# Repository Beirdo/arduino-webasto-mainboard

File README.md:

# arduino-webasto-mainboard
Custom replacement control board for Webasto Thermo Top C/E

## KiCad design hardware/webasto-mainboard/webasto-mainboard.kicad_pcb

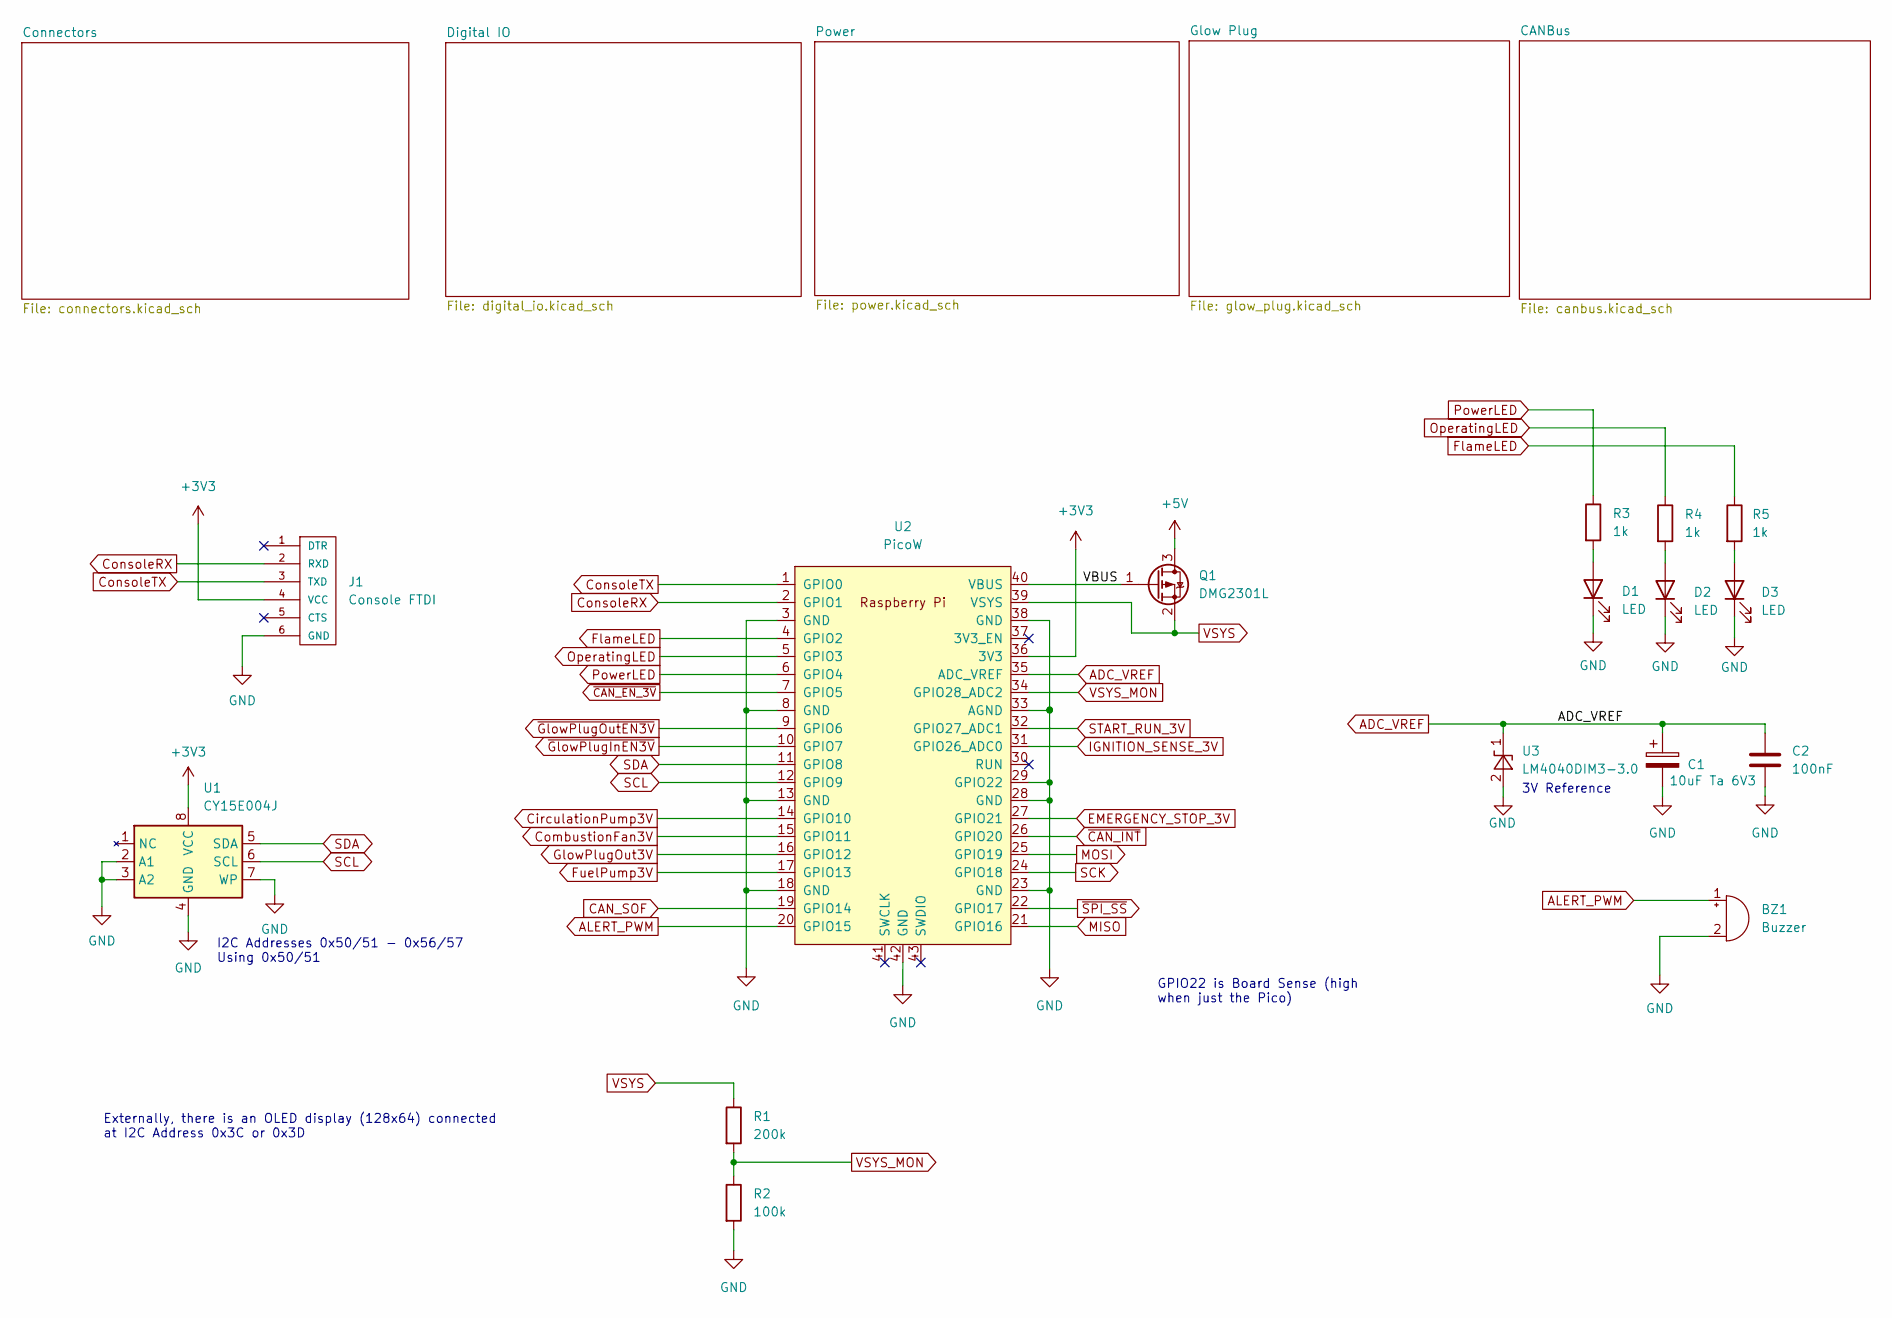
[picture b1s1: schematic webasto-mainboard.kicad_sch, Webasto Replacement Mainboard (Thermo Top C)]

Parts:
BZ1: Buzzer; Buzzer_TDK_PS1240P02BT_D12.2mm_H6.5mm
C1: 10uF Ta 6V3; CP_EIA-3216-10_Kemet-I_Pad1.58x1.35mm_HandSolder
C2: 100nF; C_0805_2012Metric_Pad1.18x1.45mm_HandSolder
D1, D2, D3: LED; LED_0805_2012Metric_Pad1.15x1.40mm_HandSolder
J1: Console FTDI; FTDI-TARGET
Q1: DMG2301L; SOT-23
R1: 200k; R_0805_2012Metric_Pad1.20x1.40mm_HandSolder
R2: 100k; R_0805_2012Metric_Pad1.20x1.40mm_HandSolder
R3, R4, R5: 1k; R_0805_2012Metric_Pad1.20x1.40mm_HandSolder
U1: CY15E004J; SOIC-8_5.23x5.23mm_P1.27mm
U2: PicoW; RPi_Pico_SMD_TH
U3: LM4040DIM3-3.0; SOT-23

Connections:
+3V3: J1.4 (VCC), U1.8 (VCC), U2.36 (3V3); also elsewhere on the board
+5V: Q1.3 (D); also elsewhere on the board
/VBUS: Q1.1 (G), U2.40 (VBUS)
ADC_VREF: C1.1, C2.1, U2.35 (ADC_VREF), U3.1 (K)
ALERT_PWM: BZ1.1 (-), U2.20 (GPIO15)
CAN_SOF: U2.19 (GPIO14); also elsewhere on the board
CirculationPump3V: U2.14 (GPIO10); also elsewhere on the board
CombustionFan3V: U2.15 (GPIO11); also elsewhere on the board
ConsoleRX: J1.2 (RXD), U2.2 (GPIO1)
ConsoleTX: J1.3 (TXD), U2.1 (GPIO0)
EMERGENCY_STOP_3V: U2.27 (GPIO21); also elsewhere on the board
FlameLED: R5.1, U2.4 (GPIO2)
FuelPump3V: U2.17 (GPIO13); also elsewhere on the board
GND: BZ1.2 (+), C1.2, C2.2, D1.1 (K), D2.1 (K), D3.1 (K), J1.6 (GND), R2.2, U1.2 (A1), U1.3 (A2), U1.4 (GND), U1.7 (WP), U2.3 (GND), U2.8 (GND), U2.13 (GND), U2.18 (GND), U2.23 (GND), U2.28 (GND), U2.29 (GPIO22), U2.33 (AGND), U2.42 (GND), U3.2 (A); also elsewhere on the board
GlowPlugOut3V: U2.16 (GPIO12); also elsewhere on the board
IGNITION_SENSE_3V: U2.31 (GPIO26_ADC0); also elsewhere on the board
MISO: U2.21 (GPIO16); also elsewhere on the board
MOSI: U2.25 (GPIO19); also elsewhere on the board
unnamed: D1.2 (A), R3.2
unnamed: D2.2 (A), R4.2
unnamed: D3.2 (A), R5.2
OperatingLED: R4.1, U2.5 (GPIO3)
PowerLED: R3.1, U2.6 (GPIO4)
SCK: U2.24 (GPIO18); also elsewhere on the board
SCL: U1.6 (SCL), U2.12 (GPIO9); also elsewhere on the board
SDA: U1.5 (SDA), U2.11 (GPIO8); also elsewhere on the board
START_RUN_3V: U2.32 (GPIO27_ADC1); also elsewhere on the board
VSYS: Q1.2 (S), R1.1, U2.39 (VSYS)
VSYS_MON: R1.2, R2.1, U2.34 (GPIO28_ADC2)
~CAN_EN_3V: U2.7 (GPIO5); also elsewhere on the board
~CAN_INT: U2.26 (GPIO20); also elsewhere on the board
~GlowPlugInEN3V: U2.10 (GPIO7); also elsewhere on the board
~GlowPlugOutEN3V: U2.9 (GPIO6); also elsewhere on the board
~SPI_SS: U2.22 (GPIO17); also elsewhere on the board

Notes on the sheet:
I2C Addresses 0x50/51 - 0x56/57 Using 0x50/51
GPIO22 is Board Sense (high when just the Pico)
Externally, there is an OLED display (128x64) connected at I2C Address 0x3C or 0x3D
3V Reference

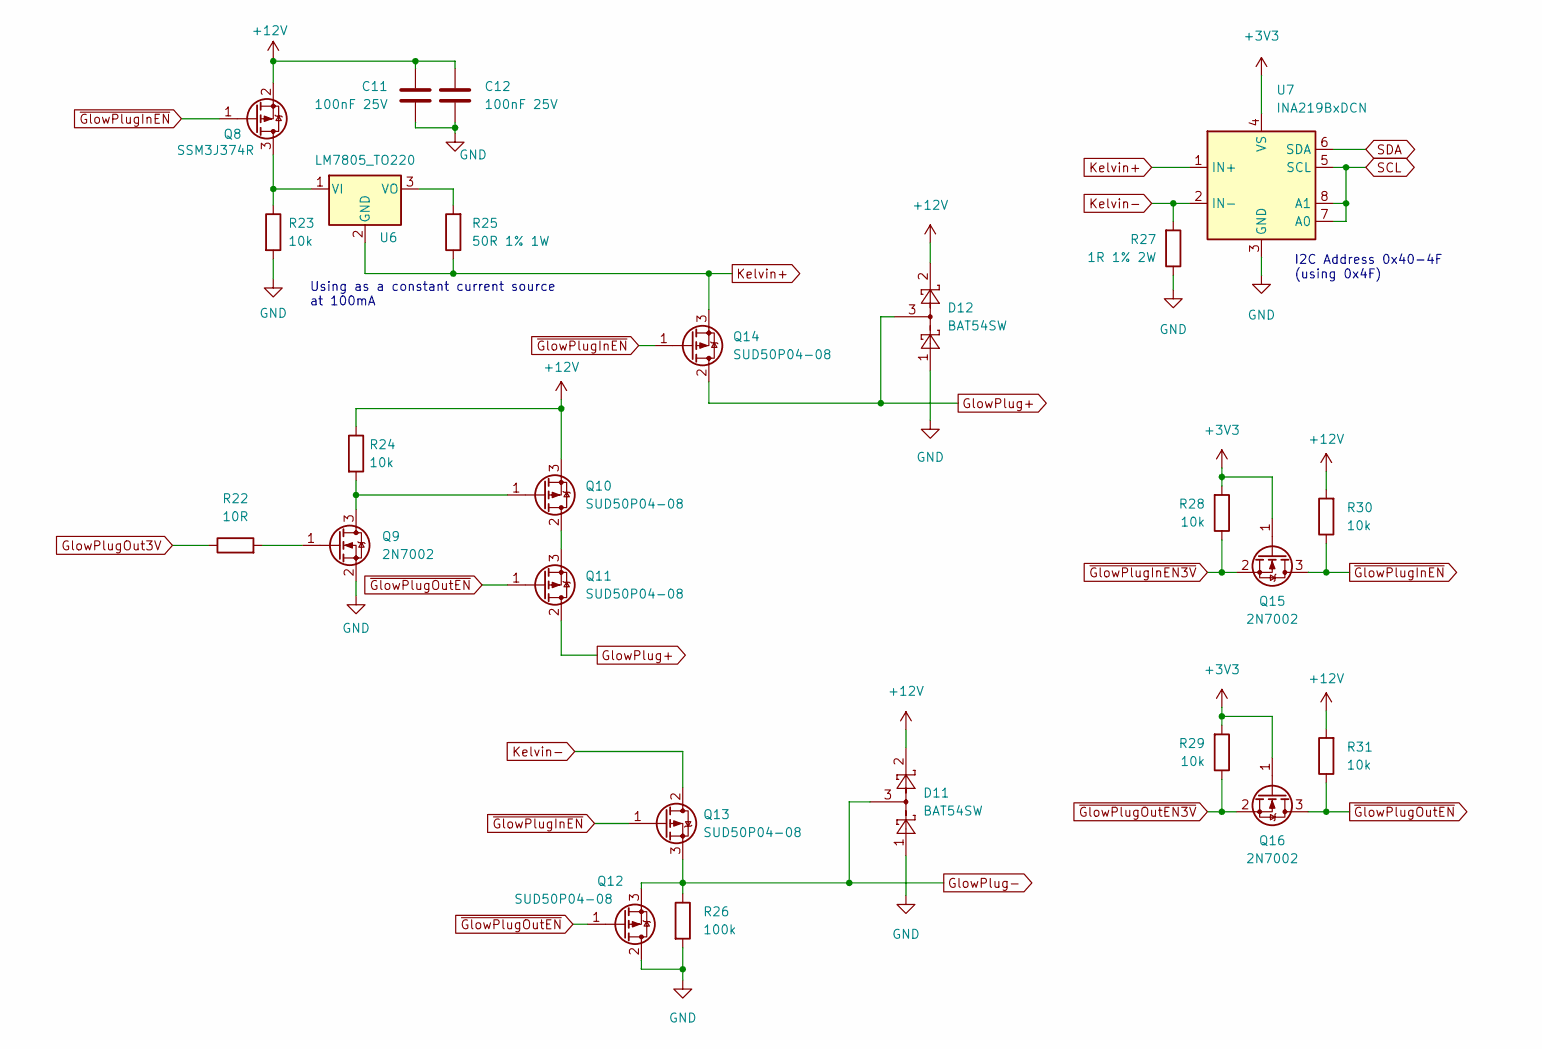
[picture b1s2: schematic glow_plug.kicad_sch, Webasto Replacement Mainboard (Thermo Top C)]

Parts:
C11, C12: 100nF 25V; C_0805_2012Metric_Pad1.18x1.45mm_HandSolder
D11, D12: BAT54SW; SOT-323_SC-70
Q8: SSM3J374R; SOT-23
Q9, Q15, Q16: 2N7002; SOT-23
Q10, Q11, Q12, Q13, Q14: SUD50P04-08; TO-252-2
R22: 10R; R_0805_2012Metric_Pad1.20x1.40mm_HandSolder
R23, R24, R28, R29, R30, R31: 10k; R_0805_2012Metric_Pad1.20x1.40mm_HandSolder
R25: 50R 1% 1W; R_2816_7142Metric_Pad3.20x4.45mm_HandSolder
R26: 100k; R_0805_2012Metric_Pad1.20x1.40mm_HandSolder
R27: 1R 1% 2W; R_2512_6332Metric_Pad1.40x3.35mm_HandSolder
U6: LM7805_TO220; TO-220-3_Vertical
U7: INA219BxDCN; SOT-23-8

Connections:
+3V3: Q15.1 (G), Q16.1 (G), R28.2, R29.2, U7.4 (VS); also elsewhere on the board
+12V: C11.2, C12.2, D11.2, D12.2, Q8.2 (S), Q10.3 (S), R24.1, R30.2, R31.2; also elsewhere on the board
GND: C11.1, C12.1, D11.1, D12.1, Q9.2 (S), Q12.2 (D), R23.2, R26.2, R27.1, U7.3 (GND); also elsewhere on the board
GlowPlug+: D12.3, Q11.2 (D), Q14.2 (D); also elsewhere on the board
GlowPlug-: D11.3, Q12.3 (S), Q13.3 (S), R26.1; also elsewhere on the board
GlowPlugOut3V: R22.1; also elsewhere on the board
Kelvin+: Q14.3 (S), R25.1, U6.2 (GND), U7.1 (IN+)
Kelvin-: Q13.2 (D), R27.2, U7.2 (IN-)
unnamed: Q8.3 (D), R23.1, U6.1 (VI)
unnamed: Q9.1 (G), R22.2
unnamed: Q9.3 (D), Q10.1 (G), R24.2
unnamed: Q10.2 (D), Q11.3 (S)
unnamed: R25.2, U6.3 (VO)
SCL: U7.5 (SCL), U7.7 (A0), U7.8 (A1); also elsewhere on the board
SDA: U7.6 (SDA); also elsewhere on the board
~GlowPlugInEN3V: Q15.2 (S), R28.1; also elsewhere on the board
~GlowPlugInEN: Q8.1 (G), Q13.1 (G), Q14.1 (G), Q15.3 (D), R30.1
~GlowPlugOutEN3V: Q16.2 (S), R29.1; also elsewhere on the board
~GlowPlugOutEN: Q11.1 (G), Q12.1 (G), Q16.3 (D), R31.1

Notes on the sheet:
I2C Address 0x40-4F (using 0x4F)
Using as a constant current source at 100mA

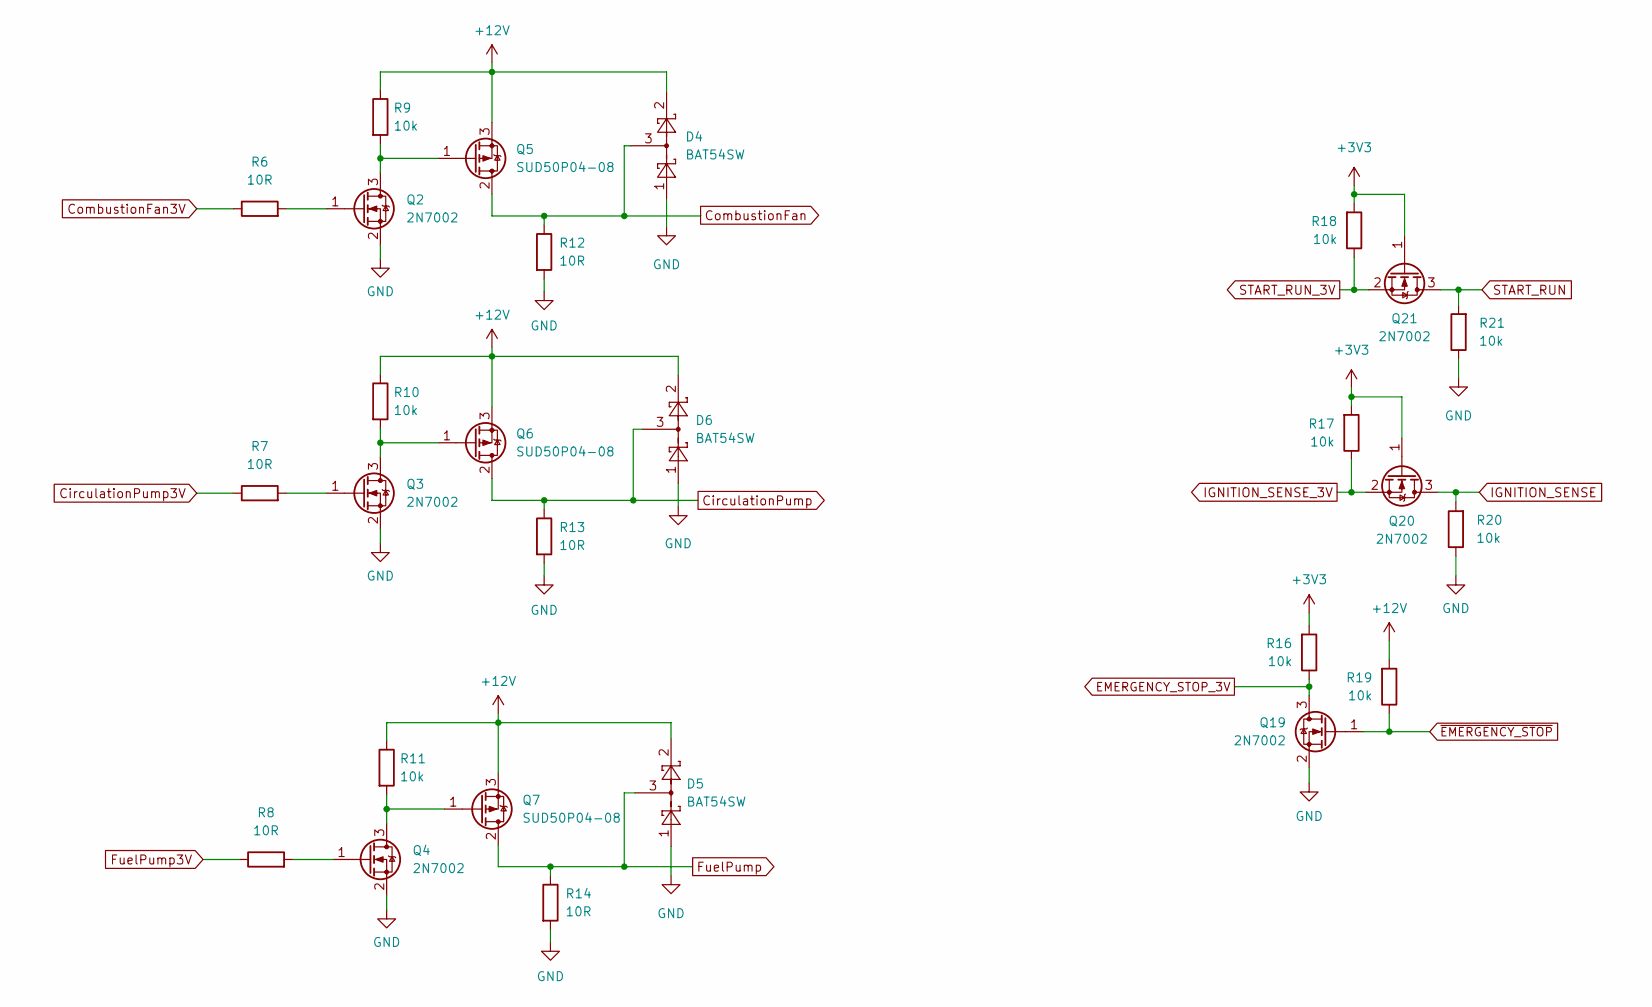
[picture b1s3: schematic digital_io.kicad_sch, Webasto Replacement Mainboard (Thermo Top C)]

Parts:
D4, D5, D6: BAT54SW; SOT-323_SC-70
Q2, Q3, Q4, Q19, Q20, Q21: 2N7002; SOT-23
Q5, Q6, Q7: SUD50P04-08; TO-252-2
R6, R7, R8, R12, R13, R14: 10R; R_0805_2012Metric_Pad1.20x1.40mm_HandSolder
R9, R10, R11, R16, R17, R18, R19, R20, R21: 10k; R_0805_2012Metric_Pad1.20x1.40mm_HandSolder

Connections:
+3V3: Q20.1 (G), Q21.1 (G), R16.2, R17.2, R18.2; also elsewhere on the board
+12V: D4.2, D5.2, D6.2, Q5.3 (S), Q6.3 (S), Q7.3 (S), R9.1, R10.1, R11.1, R19.2; also elsewhere on the board
CirculationPump: D6.3, Q6.2 (D), R13.1; also elsewhere on the board
CirculationPump3V: R7.1; also elsewhere on the board
CombustionFan: D4.3, Q5.2 (D), R12.1; also elsewhere on the board
CombustionFan3V: R6.1; also elsewhere on the board
EMERGENCY_STOP_3V: Q19.3 (D), R16.1; also elsewhere on the board
FuelPump: D5.3, Q7.2 (D), R14.1; also elsewhere on the board
FuelPump3V: R8.1; also elsewhere on the board
GND: D4.1, D5.1, D6.1, Q2.2 (S), Q3.2 (S), Q4.2 (S), Q19.2 (S), R12.2, R13.2, R14.2, R20.1, R21.1; also elsewhere on the board
IGNITION_SENSE: Q20.3 (D), R20.2; also elsewhere on the board
IGNITION_SENSE_3V: Q20.2 (S), R17.1; also elsewhere on the board
unnamed: Q2.1 (G), R6.2
unnamed: Q2.3 (D), Q5.1 (G), R9.2
unnamed: Q3.1 (G), R7.2
unnamed: Q3.3 (D), Q6.1 (G), R10.2
unnamed: Q4.1 (G), R8.2
unnamed: Q4.3 (D), Q7.1 (G), R11.2
START_RUN: Q21.3 (D), R21.2; also elsewhere on the board
START_RUN_3V: Q21.2 (S), R18.1; also elsewhere on the board
~EMERGENCY_STOP: Q19.1 (G), R19.1; also elsewhere on the board

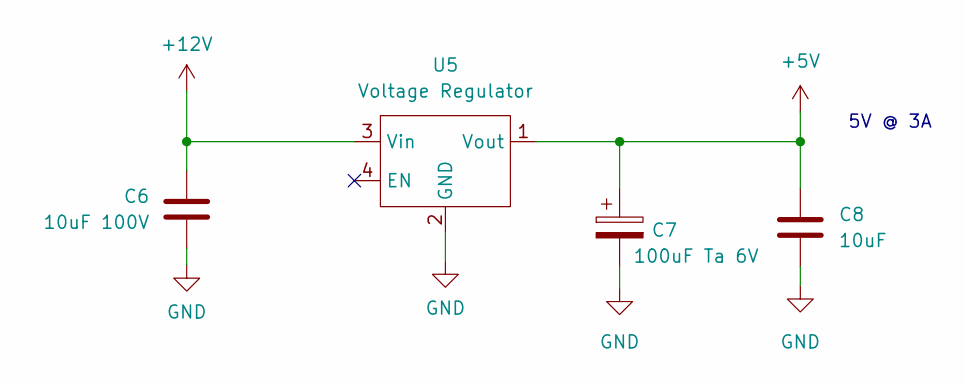
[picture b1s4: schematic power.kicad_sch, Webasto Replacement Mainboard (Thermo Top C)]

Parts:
C6: 10uF 100V; C_1210_3225Metric_Pad1.33x2.70mm_HandSolder
C7: 100uF Ta 6V; CP_EIA-3216-10_Kemet-I_Pad1.58x1.35mm_HandSolder
C8: 10uF; C_0805_2012Metric_Pad1.18x1.45mm_HandSolder
U5: Voltage Regulator; Switching_Regulator_Module

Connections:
+5V: C7.1, C8.1, U5.1 (Vout); also elsewhere on the board
+12V: C6.1, U5.3 (Vin); also elsewhere on the board
GND: C6.2, C7.2, C8.2, U5.2 (GND); also elsewhere on the board

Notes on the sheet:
5V @ 3A

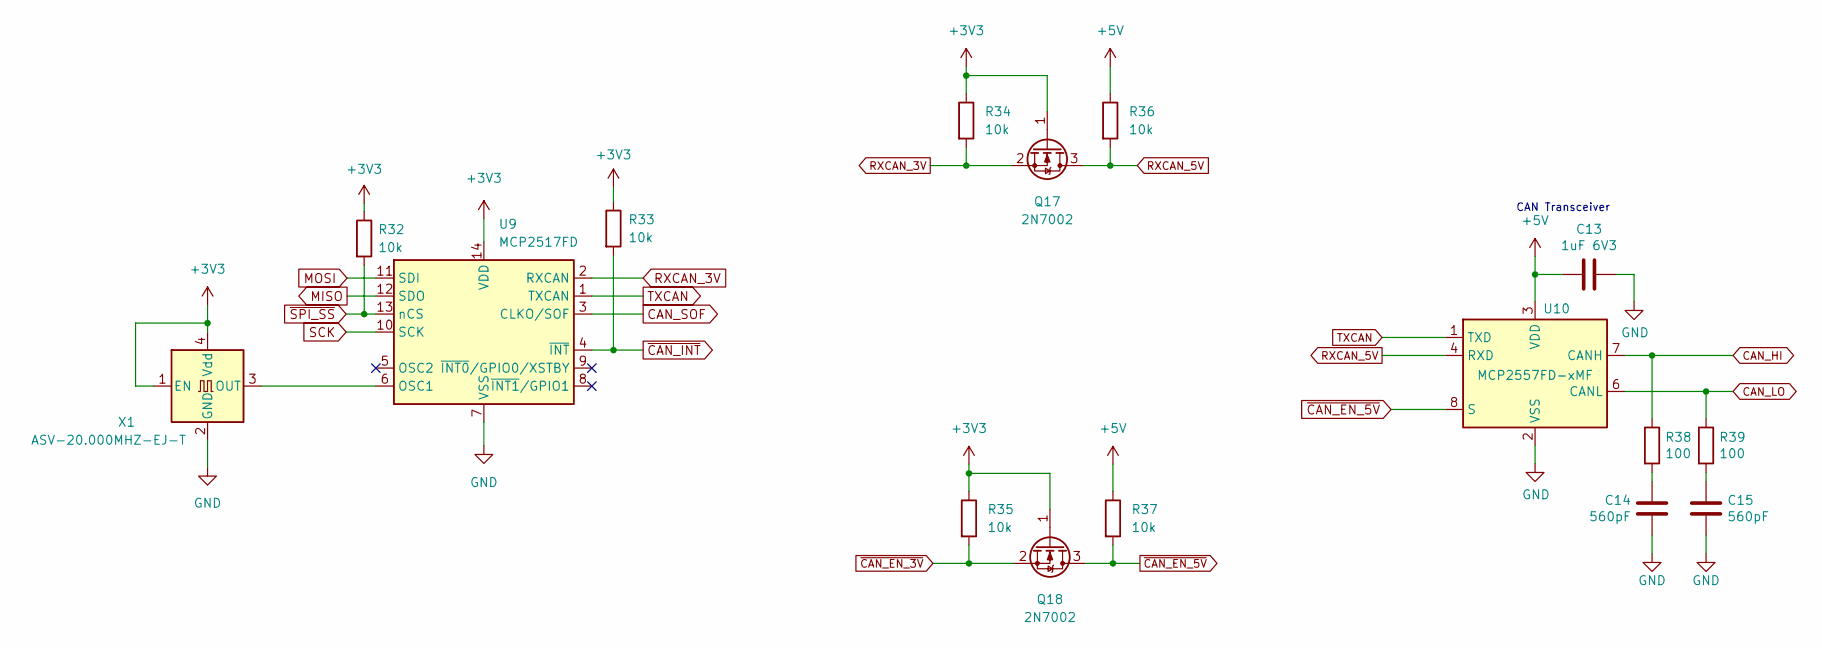
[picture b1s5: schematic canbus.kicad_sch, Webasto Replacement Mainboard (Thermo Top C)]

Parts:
C13: 1uF 6V3; C_0805_2012Metric_Pad1.18x1.45mm_HandSolder
C14, C15: 560pF; C_0805_2012Metric_Pad1.18x1.45mm_HandSolder
Q17, Q18: 2N7002; SOT-23
R32, R33, R34, R35, R36, R37: 10k; R_0805_2012Metric_Pad1.20x1.40mm_HandSolder
R38, R39: 100; R_0805_2012Metric_Pad1.20x1.40mm_HandSolder
U9: MCP2517FD; SOIC-14_3.9x8.7mm_P1.27mm
U10: MCP2557FD-xMF; SOIC-8_3.9x4.9mm_P1.27mm
X1: ASV-20.000MHZ-EJ-T; Oscillator_SMD_Abracon_ASV-4Pin_7.0x5.1mm

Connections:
+3V3: Q17.1 (G), Q18.1 (G), R32.1, R33.1, R34.1, R35.1, U9.14 (VDD), X1.1 (EN), X1.4 (Vdd); also elsewhere on the board
+5V: C13.2, R36.1, R37.1, U10.3 (VDD); also elsewhere on the board
CAN_HI: R38.1, U10.7 (CANH); also elsewhere on the board
CAN_LO: R39.1, U10.6 (CANL); also elsewhere on the board
CAN_SOF: U9.3 (CLKO/SOF); also elsewhere on the board
GND: C13.1, C14.1, C15.2, U9.7 (VSS), U10.2 (VSS), U10.9 (VSS), X1.2 (GND); also elsewhere on the board
MISO: U9.12 (SDO); also elsewhere on the board
MOSI: U9.11 (SDI); also elsewhere on the board
unnamed: C14.2, R38.2
unnamed: C15.1, R39.2
unnamed: U9.6 (OSC1), X1.3 (OUT)
RXCAN_3V: Q17.2 (S), R34.2, U9.2 (RXCAN)
RXCAN_5V: Q17.3 (D), R36.2, U10.4 (RXD)
SCK: U9.10 (SCK); also elsewhere on the board
TXCAN: U9.1 (TXCAN), U10.1 (TXD)
~CAN_EN_3V: Q18.2 (S), R35.2; also elsewhere on the board
~CAN_EN_5V: Q18.3 (D), R37.2, U10.8 (S)
~CAN_INT: R33.2, U9.4 (~INT); also elsewhere on the board
~SPI_SS: R32.2, U9.13 (nCS); also elsewhere on the board

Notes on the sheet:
CAN Transceiver

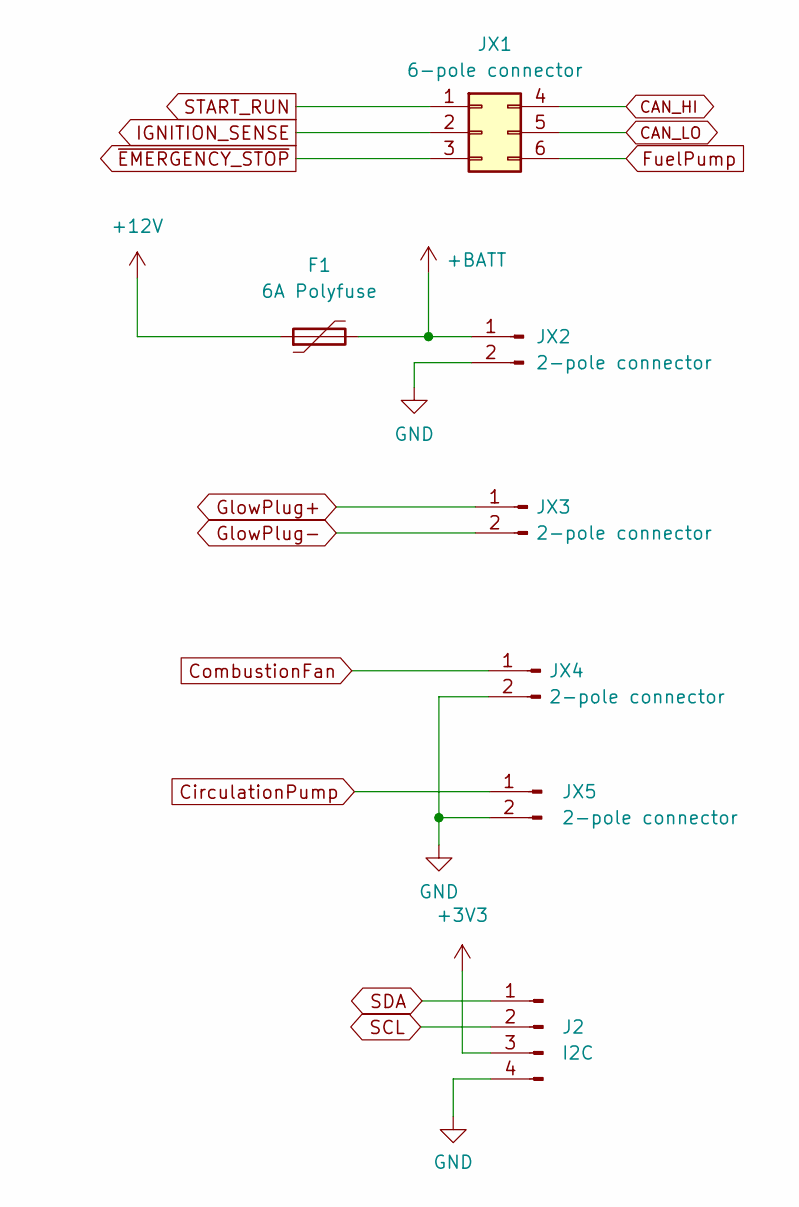
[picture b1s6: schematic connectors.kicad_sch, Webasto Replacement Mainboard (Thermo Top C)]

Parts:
F1: 6A Polyfuse; R_1812_4532Metric_Pad1.30x3.40mm_HandSolder; Digikey F2772CT-ND
J2: I2C; PinHeader_1x04_P2.54mm_Vertical
JX1: 6-pole connector; Webasto_Therma_Top_C_X1
JX2: 2-pole connector; Webasto_Therma_Top_C_X2
JX3: 2-pole connector; Webasto_Therma_Top_C_X3
JX4, JX5: 2-pole connector; Webasto_Therma_Top_C_X4X5

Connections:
+3V3: J2.3; also elsewhere on the board
+12V: F1.1; also elsewhere on the board
+BATT: F1.2, JX2.1
CAN_HI: JX1.4; also elsewhere on the board
CAN_LO: JX1.5; also elsewhere on the board
CirculationPump: JX5.1; also elsewhere on the board
CombustionFan: JX4.1; also elsewhere on the board
FuelPump: JX1.6; also elsewhere on the board
GND: J2.4, JX2.2, JX4.2, JX5.2; also elsewhere on the board
GlowPlug+: JX3.1; also elsewhere on the board
GlowPlug-: JX3.2; also elsewhere on the board
IGNITION_SENSE: JX1.2; also elsewhere on the board
SCL: J2.2; also elsewhere on the board
SDA: J2.1; also elsewhere on the board
START_RUN: JX1.1; also elsewhere on the board
~EMERGENCY_STOP: JX1.3; also elsewhere on the board

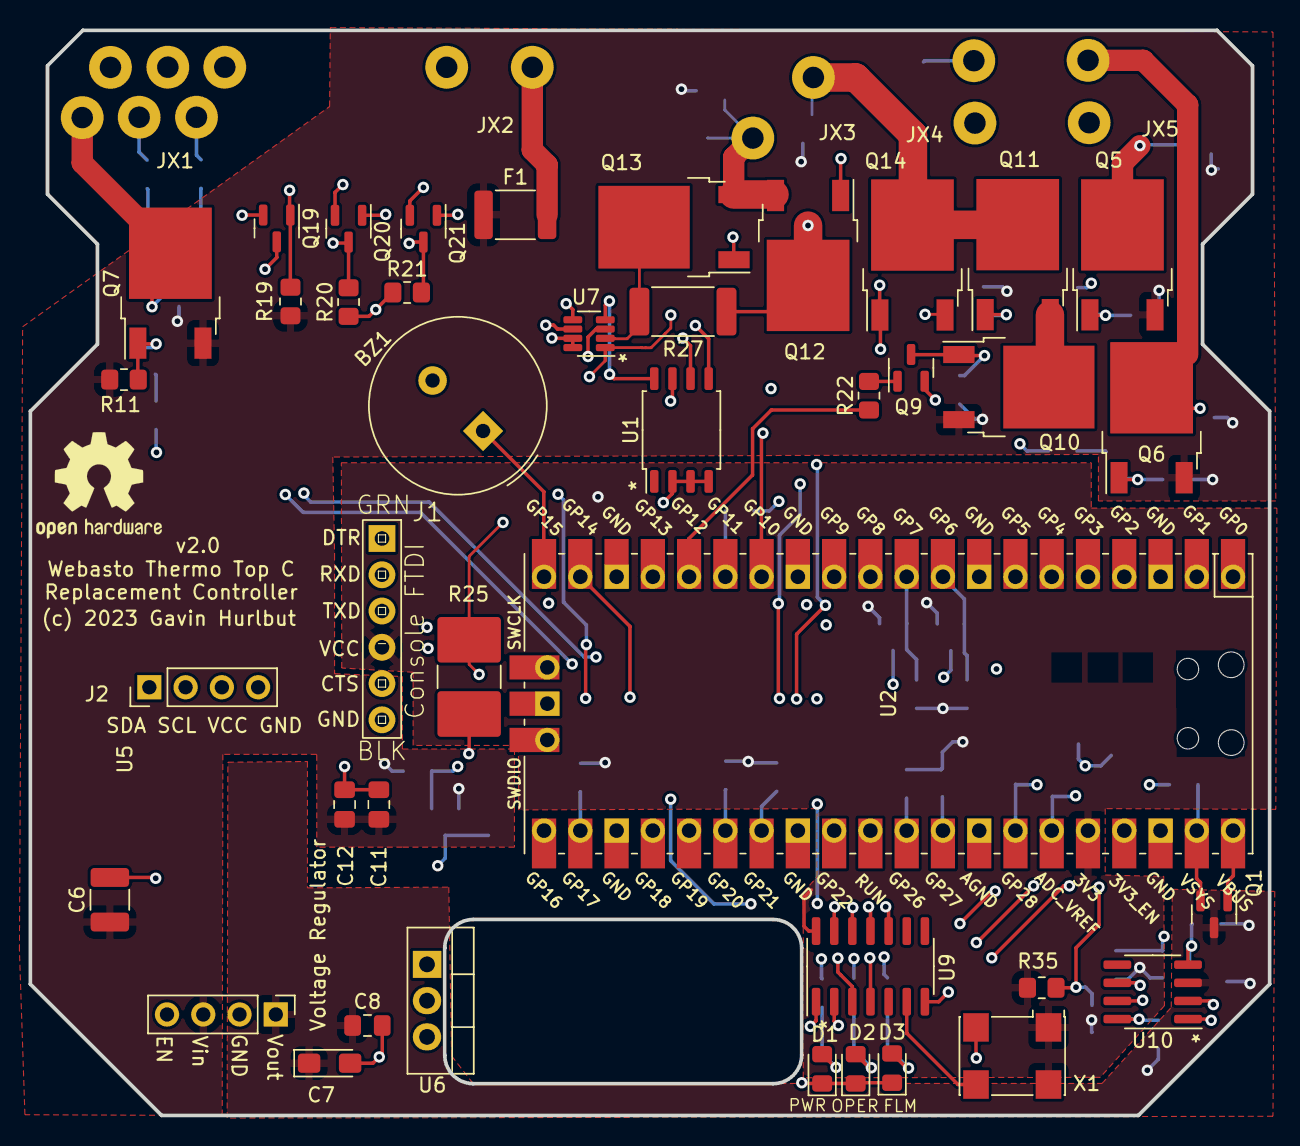
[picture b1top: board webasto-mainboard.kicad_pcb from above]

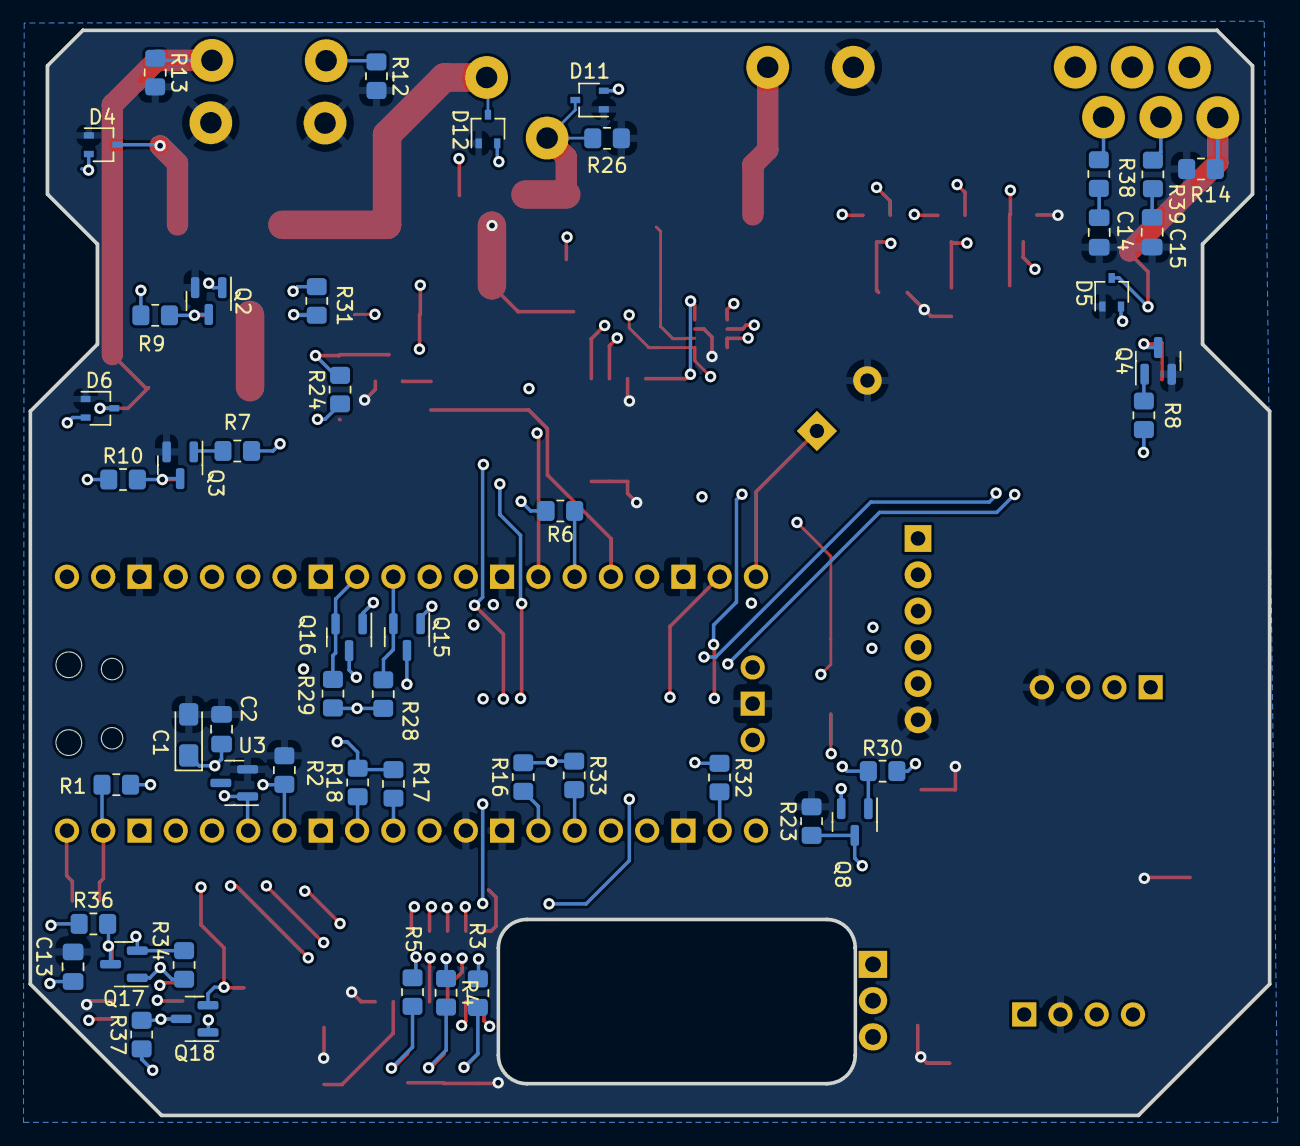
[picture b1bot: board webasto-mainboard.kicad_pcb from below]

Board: 4 copper layers, 86.8 x 76.0 mm, 95 parts (49 on the bottom side), 68 nets.

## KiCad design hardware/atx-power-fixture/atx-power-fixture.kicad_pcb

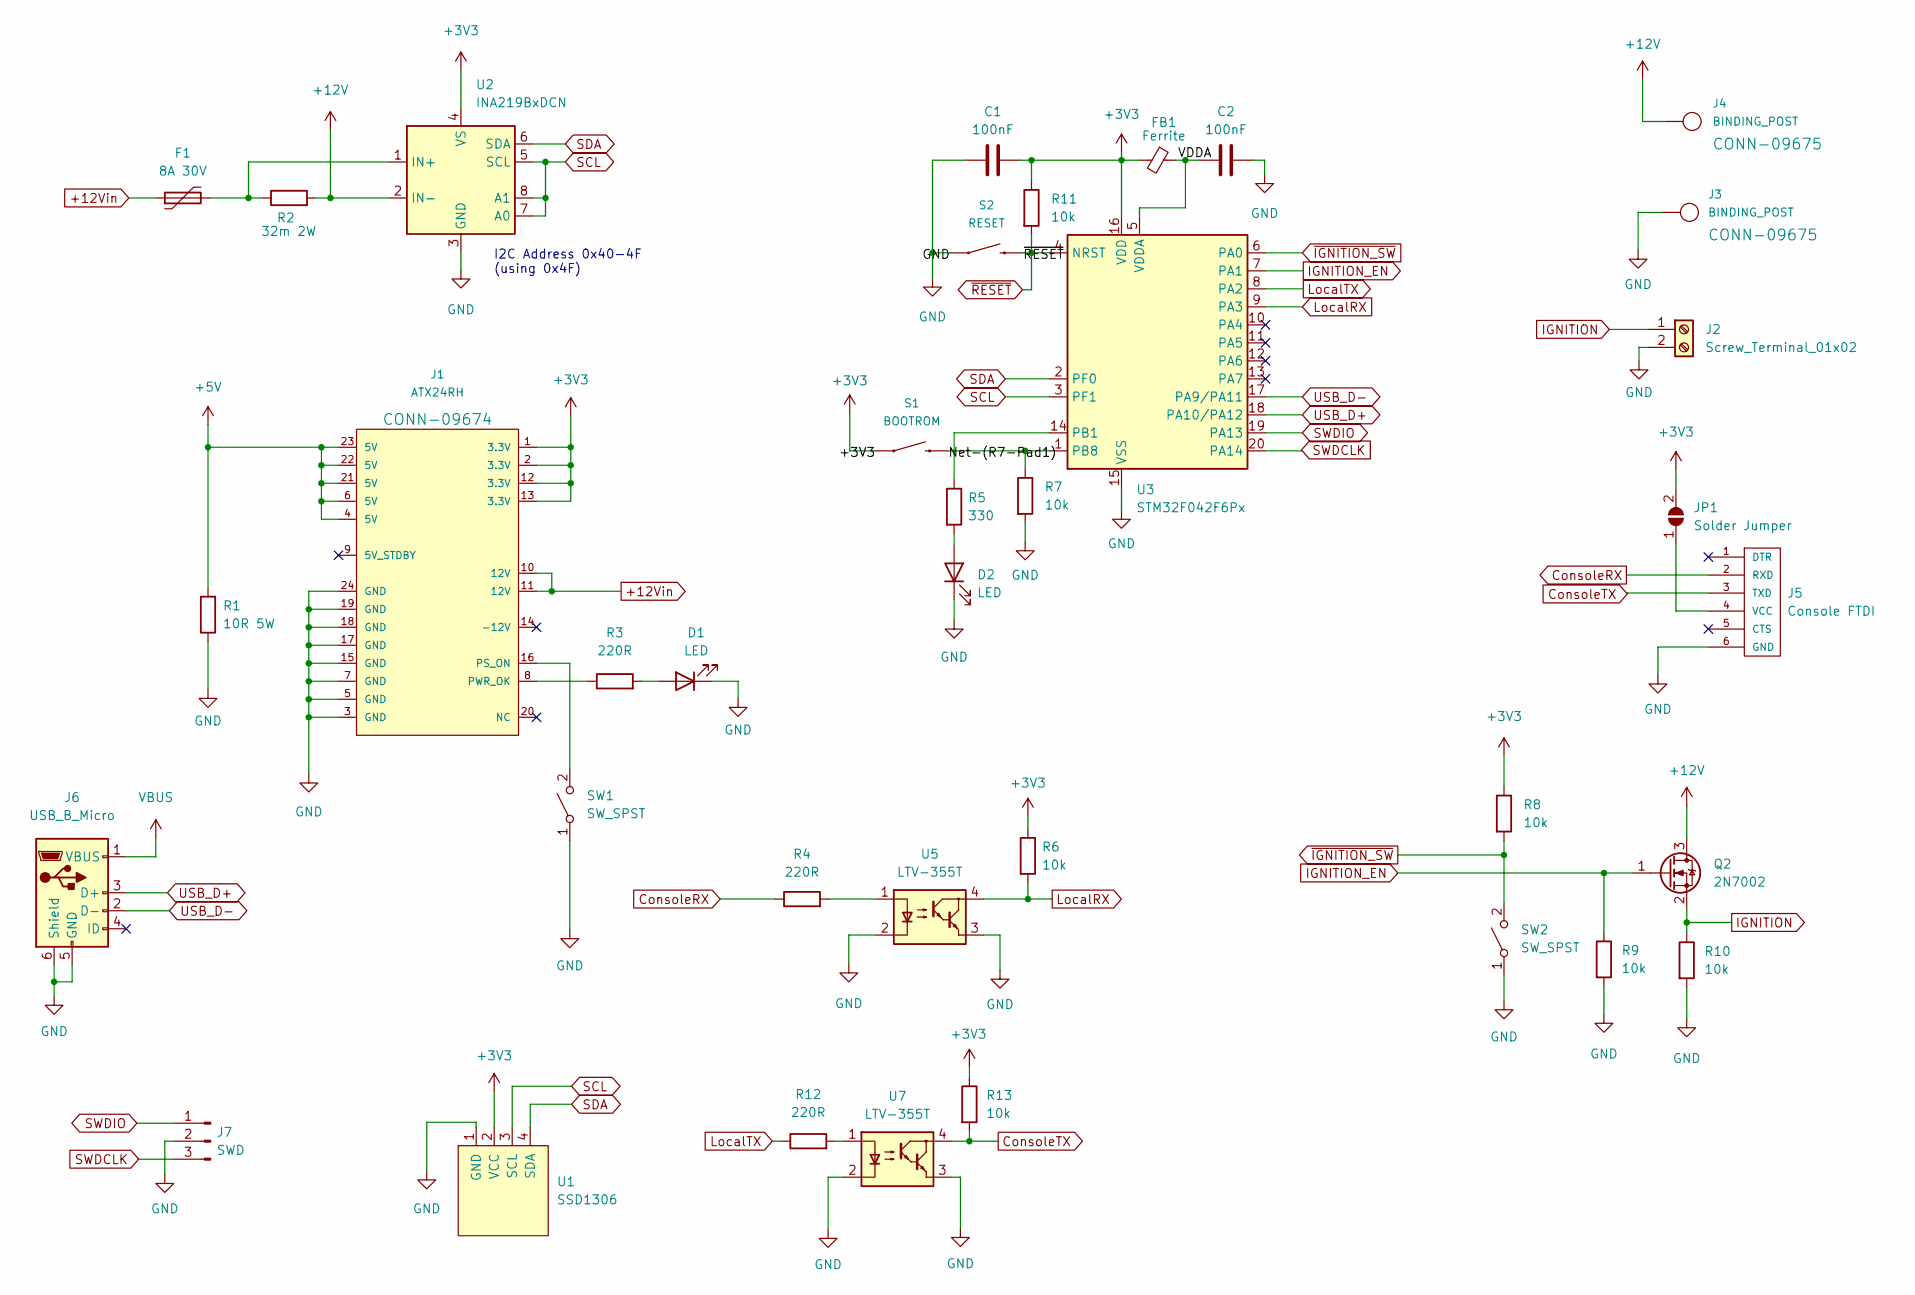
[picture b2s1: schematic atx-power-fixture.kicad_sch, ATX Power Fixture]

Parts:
C1, C2: 100nF; C_0805_2012Metric_Pad1.18x1.45mm_HandSolder
D1: LED; LED_D3.0mm
D2: LED; LED_0805_2012Metric_Pad1.15x1.40mm_HandSolder
F1: 8A 30V; Fuse_Littelfuse_372_D8.50mm
FB1: Ferrite; L_0805_2012Metric_Pad1.15x1.40mm_HandSolder
J1: ATX24RH; ATX24_RIGHT_ANGLE
J2: Screw_Terminal_01x02; TerminalBlock_TE_282834-2_1x02_P2.54mm_Horizontal
J3, J4: BINDING_POST
J5: Console FTDI; FTDI-TARGET
J6: USB_B_Micro; USB_Micro-B_Amphenol_10118194_Horizontal
J7: SWD; PinHeader_1x03_P2.54mm_Vertical
JP1: Solder Jumper; SolderJumper-2_P1.3mm_Open_TrianglePad1.0x1.5mm
Q2: 2N7002; SOT-23
R1: 10R 5W; 355010RFT
R2: 32m 2W; R_1812_4532Metric_Pad1.30x3.40mm_HandSolder
R3, R4, R12: 220R; R_0805_2012Metric_Pad1.20x1.40mm_HandSolder
R5: 330; R_0805_2012Metric_Pad1.20x1.40mm_HandSolder
R6, R7, R8, R9, R10, R11, R13: 10k; R_0805_2012Metric_Pad1.20x1.40mm_HandSolder
S1: BOOTROM; TACTILE_SWITCH_PTH_6.0MM
S2: RESET; TACTILE_SWITCH_PTH_6.0MM
SW1, SW2: SW_SPST; SWITCH_SPDT_PTH_11.6X4.0MM
U1: SSD1306; 128x64OLED
U2: INA219BxDCN; SOT-23-8
U3: STM32F042F6Px; TSSOP-20_4.4x6.5mm_P0.65mm
U5, U7: LTV-355T; SO-4_4.4x3.6mm_P2.54mm

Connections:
+3V3: C1.2, FB1.2, J1.1 (3.3V), J1.2 (3.3V), J1.12 (3.3V), J1.13 (3.3V), JP1.2 (B), R6.1, R8.1, R11.1, R13.1, S1.1, S1.2 (1), U1.2 (VCC), U2.4 (VS), U3.16 (VDD)
+5V: J1.4 (5V), J1.6 (5V), J1.21 (5V), J1.22 (5V), J1.23 (5V), R1.2
+12V: J4.P$1, Q2.3 (D), R2.2, U2.2 (IN-)
+12Vin: F1.1, J1.10 (12V), J1.11 (12V)
/VDDA: C2.1, FB1.1, U3.5 (VDDA)
ConsoleRX: J5.2 (RXD), R4.1
ConsoleTX: J5.3 (TXD), R13.2, U7.4
GND: C1.1, C2.2, D1.1 (K), D2.1 (K), J1.3 (GND), J1.5 (GND), J1.7 (GND), J1.15 (GND), J1.17 (GND), J1.18 (GND), J1.19 (GND), J1.24 (GND), J2.2, J3.P$1, J5.6 (GND), J6.5 (GND), J6.6 (Shield), J7.2, R1.1, R7.2, R9.2, R10.2, S2.1, S2.2 (1), SW1.1 (A), SW2.1 (A), U1.1 (GND), U2.3 (GND), U3.15 (VSS), U5.2, U5.3, U7.2, U7.3
IGNITION: J2.1, Q2.2 (S), R10.1
IGNITION_EN: Q2.1 (G), R9.1, U3.7 (PA1)
LocalRX: R6.2, U3.9 (PA3), U5.4
LocalTX: R12.1, U3.8 (PA2)
unnamed: D1.2 (A), R3.2
unnamed: D2.2 (A), R5.2
unnamed: F1.2, R2.1, U2.1 (IN+)
unnamed: J1.8 (PWR_OK), R3.1
unnamed: J1.16 (PS_ON), SW1.2 (B)
unnamed: J5.4 (VCC), JP1.1 (A)
unnamed: R4.2, U5.1
unnamed: R5.1, U3.14 (PB1)
unnamed: R12.2, U7.1
SCL: U1.3 (SCL), U2.5 (SCL), U2.7 (A0), U2.8 (A1), U3.3 (PF1)
SDA: U1.4 (SDA), U2.6 (SDA), U3.2 (PF0)
SWDCLK: J7.3, U3.20 (PA14)
SWDIO: J7.1, U3.19 (PA13)
USB_D+: J6.3 (D+), U3.18 (PA10/PA12)
USB_D-: J6.2 (D-), U3.17 (PA9/PA11)
VBUS: J6.1 (VBUS)
~IGNITION_SW: R8.2, SW2.2 (B), U3.6 (PA0)
~RESET: R11.2, S2.3 (2), S2.4 (2), U3.4 (NRST)

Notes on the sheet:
I2C Address 0x40-4F (using 0x4F)

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

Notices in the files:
hardware/atx-power-fixture/atx-power-fixture.kicad_pcb:
(c) 2023 Gavin Hurlbut
hardware/qwiic-interface/qwiic-interface.kicad_pcb:
v2.0 (c) 2023
parts and their libraries:
Copyright 2021 Accelerated Designs. All rights reserved.
